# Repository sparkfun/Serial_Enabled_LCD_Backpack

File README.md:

Serial Enabled LCD Backpack
===========================

[*Serial Enabled LCD Backpack (LCD-00258)*](https://www.sparkfun.com/products/258)

This PIC-based serial enabled LCD backpack allows you to control a parallel based LCD over a single-wire serial interface. It is compatible with 16x2 LCDs and 20x4 LCDs.

Repository Contents
-------------------

* **/Firmware**
  * **/Arduino_Examples** - Arduino example code to control the PIC-based serial enabled LCD
  * **/Default_Firmware** - Any default firmware on the PIC that the part ships with for different size LCD screens
* **/Hardware** - All Eagle design files (.brd, .sch, .STL)

Documentation
--------------
* **[Hookup Guide](https://learn.sparkfun.com/tutorials/pic-based-serial-enabled-character-lcd-hookup-guide)** - Basic hookup guide for the PIC-based serial enabled LCD backpack.

Product Versions
----------------

* [LCD-00258](https://www.sparkfun.com/products/258) - SparkFun Serial Enabled LCD Backpack

* Built-In Serial Enabled LCD
  * [LCD-09067](https://www.sparkfun.com/products/9067) - Built-In SparkFun Serial Enabled 16x2 LCD - White on Black 3.3V
  * [LCD-09066](https://www.sparkfun.com/products/9066) - Built-In SparkFun Serial Enabled 16x2 LCD - Black on Green 3.3V
  * [LCD-09068](https://www.sparkfun.com/products/9068) - Built-In SparkFun Serial Enabled 16x2 LCD - Red on Black 3.3V
  * [LCD-09395](https://www.sparkfun.com/products/9395) - Built-In SparkFun Serial Enabled 16x2 LCD - Whote on Black 5V
  * [LCD-09568](https://www.sparkfun.com/products/9568) - Built-In SparkFun Serial Enabled 20x4 LCD - Black on Green 5V
  * [LCD-09394](https://www.sparkfun.com/products/9394) - Built-In SparkFun Serial Enabled 16x2 LCD - Red on Black 5V

License Information
-------------------
The hardware is released under [Creative Commons ShareAlike 4.0 International](https://creativecommons.org/licenses/by-sa/4.0/).
The code is beerware; if you see me (or any other SparkFun employee) at the local, and you've found our code helpful, please buy us a round!

Distributed as-is; no warranty is given.

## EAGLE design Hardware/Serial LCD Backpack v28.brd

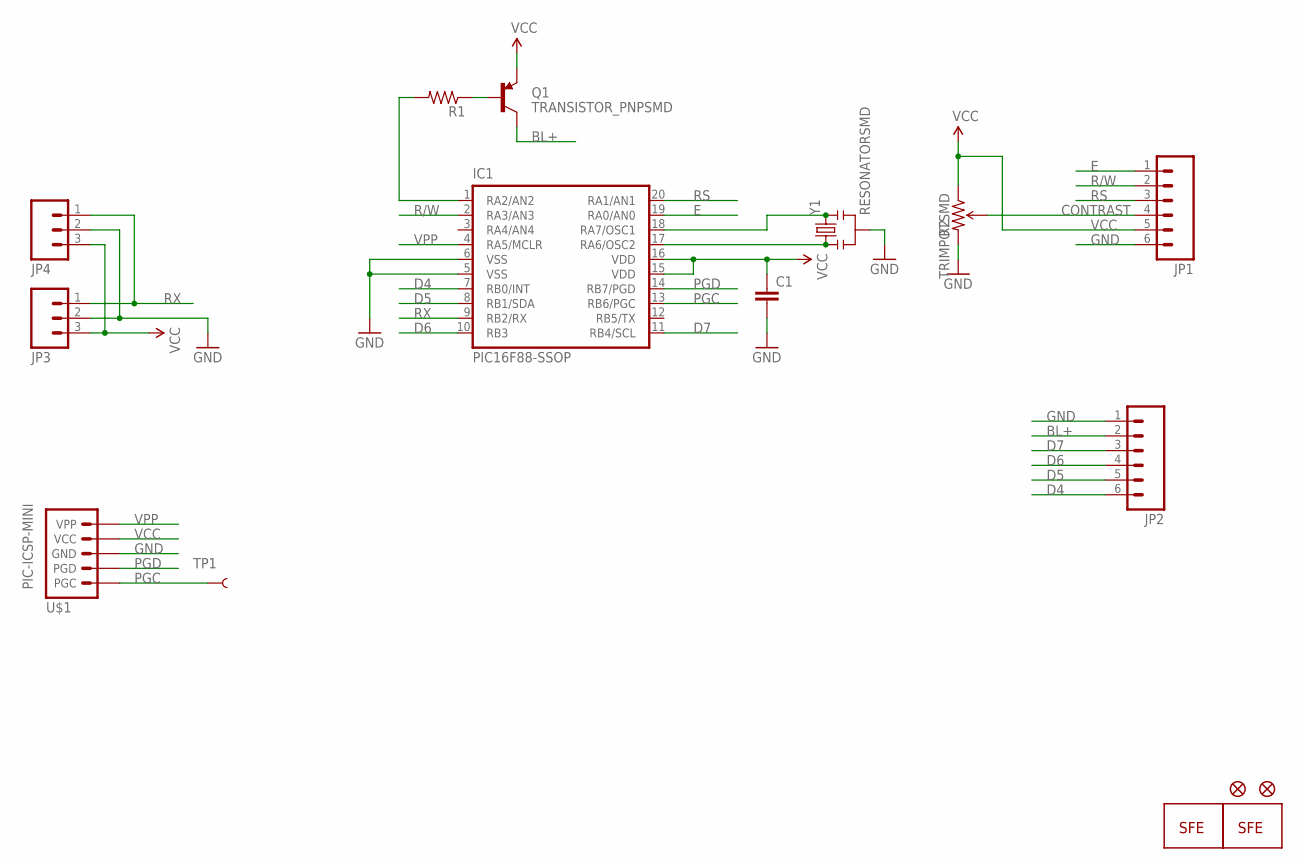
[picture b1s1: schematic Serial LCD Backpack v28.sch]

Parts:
C1: CAP0402-CAP; 0402-CAP
IC1: PIC16F88-SSOP; SSOP20
JP1, JP2: M06LOCK; 1X06_LOCK
JP3: M03PTH; 1X03
JP4: M03SCREW_LOCK; SCREWTERMINAL-3.5MM-3_LOCK.007S
Q1: TRANSISTOR_PNPSMD; SOT23-3
R1: RESISTOR0402-RES; 0402-RES
R2: TRIMPOTSMD; TRIMPOT-3MM
TP1: TEST-POINT3X5; PAD.03X.05
U$1: PIC-ICSP-MINI
U$2: LOGO-FLAME-LARGE
U$3, U$4: FIDUCIAL1X2; FIDUCIAL-1X2
U$5: LOGO-SFENEW; SFE-NEW-WEBLOGO
Y1: RESONATORSMD; RESONATOR-SMD

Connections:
BL+: JP2.2, Q1.3 (C)
CONTRAST: JP1.4, R2.2 (WIPER)
D4: IC1.7 (RB0/INT), JP2.6
D5: IC1.8 (RB1/SDA), JP2.5
D6: IC1.10 (RB3), JP2.4
D7: IC1.11 (RB4/SCL), JP2.3
E: IC1.19 (RA0/AN0), JP1.1
GND: C1.2, IC1.5 (VSS), IC1.6 (VSS), JP1.6, JP2.1, JP3.2, JP4.2, R2.3 (CW), U$1.3 (GND), Y1.2
unnamed: IC1.18 (RA7/OSC1), Y1.3
unnamed: IC1.17 (RA6/OSC2), Y1.1
unnamed: IC1.1 (RA2/AN2), R1.2
unnamed: Q1.1 (B), R1.1
PGC: IC1.13 (RB6/PGC), TP1.P$1, U$1.5 (PGC)
PGD: IC1.14 (RB7/PGD), U$1.4 (PGD)
R/W: IC1.2 (RA3/AN3), JP1.2
RS: IC1.20 (RA1/AN1), JP1.3
RX: IC1.9 (RB2/RX), JP3.1, JP4.1
VCC: C1.1, IC1.15 (VDD), IC1.16 (VDD), JP1.5, JP3.3, JP4.3, Q1.2 (E), R2.1 (CCW), U$1.2 (VCC)
VPP: IC1.4 (RA5/MCLR), U$1.1 (VPP)

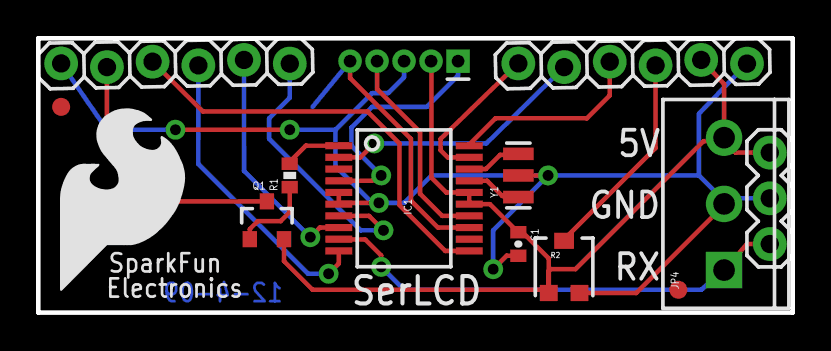
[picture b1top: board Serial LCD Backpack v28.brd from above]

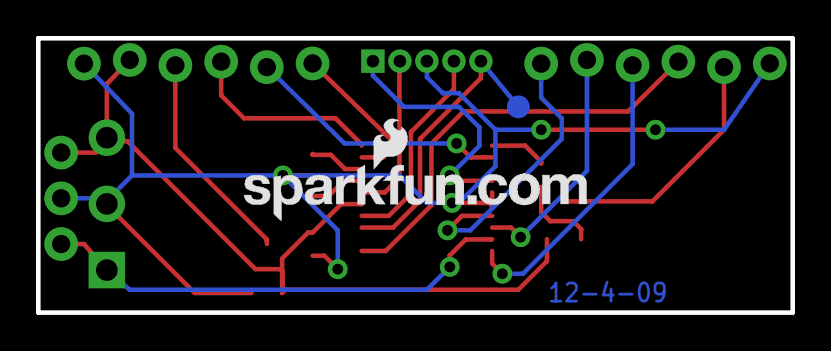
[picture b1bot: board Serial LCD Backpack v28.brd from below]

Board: 2 copper layers, 41.9 x 15.2 mm, 16 parts (2 on the bottom side), 19 nets.

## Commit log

2014-02-21 Initial hardware and firmware files commited
2018-05-04 Add files via upload
    Adding older production default firmware as backup.
2018-05-04 Rename Firmware/serlcd-v2_6_2line_10MHz.hex to Firmware/serlcd-v2_6_2line_10MHz/serlcd-v2_6_2line_10MHz.hex
2018-05-04 Rename Firmware/Arduino_examples/SerLCD_Demo/SerLCD_Demo.ino to Firmware/Arduino_examples/3_SerLCD_Demo/3_SerLCD_Demo.ino
2018-05-18 Change File Paths
    * Update folder names
    * Move default firmware into folder
2018-05-18 Update Example 1
    Update example 1 to reflect the image in the tutorial.
2018-05-18 Update Example 2
    Update example 2 file name. It was not opening correctly with the Arduino IDE.
2018-05-18 Update Example 3 Comments
    * Correct spelling and grammar.
    * Auto indent code
2018-05-18 Issue with Paths
2018-05-18 Update Arduino Paths to Same Folder
2020-11-08 Update hookup guide link
